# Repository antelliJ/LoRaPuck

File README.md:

# ESP32-C3 Lora Puck Device
https://github.com/antelliJ/LoRaPuck

A LoRa project built using an esp32-c3 supermini and an SX1262 for LoRa communication

## Features
- LoRa
    - Transmits +22 Dbm
    - 150-960 MHz
    - IPEX SMD connector
- Bluetooth Low Energy (BLE)
- WiFi (not implemented)
- 0.96" OLED display (optional)
    - I2C SSD1306

## Usage and info
there isn't a battery configuration setup, so everything is powered by wire. Check out the installation instructions below on further details on flashing builds.

### Purpose
LoRa and MeshCore are cool projects that use radio in an interesting way, and have a decently low barrier to entry with all the tools available. This project is the product of that.

## Hardware
- esp32-c3 supermini
- SX1262
- Generic SSD1306 0.96" OLED display modules with 2.54mm pin headers

## Firmware
### Schematic

### GPIO Assignment

| Signal   |   | ESP32-C3 GPIO |
|----------|---|---------------|
| SX NRST  |   | GPIO 5        |
| SX MISO  |   | GPIO 6        |
| SX MOSI  |   | GPIO 7        |
| SX NSS   |   | GPIO 10       |
| SX SCLK  |   | GPIO 1        |
| SX DIO1  |   | GPIO 0        |
| SX BUSY  |   | GPIO 4        |
|          |   |               |
| OLED SCL |   | GPIO 8        |
| OLED SDA |   | GPIO 3        |

### Installation Instructions

### For most people (recommended)
Get the latest stable firmware from the [Releases Page](https://github.com/antelliJ/LoRaPuck/releases)

The [Mescore flasher](https://meshcore.io/flasher) also has the ability to flash custom `.bin` files, so you can flash the bin files to your device there

This is paired with a MeshCore Client, for instance through the web, the mobile app, or for PC

Using the companion BLE build, you can flash firmware that you can connect to with your phone.
From here it should be able to be the same as any other campanion MeshCore device.

### For Devs
- Install [PlatformIO](https://docs.platformio.org/) in VS Code
- Clone the repository, and build and run one of the configurations through PlatformIO

- or to build a merged bin, run: (replace `AntelliPuck_companion_radio_ble` with the environment you want to build)
`pio pkg exec -p tool-esptoolpy -- esptool.py --chip esp32 merge_bin -o merged.bin --flash_mode dio --flash_size 4MB 0x0 .pio/build/AntelliPuck_companion_radio_ble/bootloader.bin 0x8000 .pio/build/AntelliPuck_companion_radio_ble/partitions.bin 0x10000 .pio/build/AntelliPuck_companion_radio_ble/firmware.bin`

### MeshCore Compatability
Theoretically it should work like any other MeshCore project, I'd personally go with the companion app for ease of communication.

## PCB
`\PCB\` includes files relevant for the schematic, PCB design, and manufacturing. 
`\PCB\production\` are the files used for PCB manufacturing

### PCB Renders

## CAD Model

Files for a model for the enclosure for this project can be found in `\3dModel\`.
`\3dModel\` is intended for all 3d printed related files.
`\3dModel\editable\` contains the editable files made in freecad for the enclosure
`\3dModel\printable\` contains the print ready files as a `.3mf` file

## Bill of Materials
A nicely formatted excel sheet is provided at `\PCB\production\ereader-bom.xlsx` with a few more comments. 
The below is just a static version of that...

| Designator  | Footprint                           | Quantity | Value             | LCSC Part # | Other Notes                                                                                                    |
|-------------|-------------------------------------|----------|-------------------|-------------|----------------------------------------------------------------------------------------------------------------|
| AE1         | U.FL_Hirose_U.FL-R-SMT-1_Vertical   | 1        | Antenna           | C88374      | Regular UFL / IPEX connector                                                                                   |
| C1, C2      | 402                                 | 2        | 100nF             |             |                                                                                                                |
| C10, C11    | 402                                 | 2        | 4.7pF             |             |                                                                                                                |
| C12, C13    | 402                                 | 2        | 1.5pF             |             |                                                                                                                |
| C14         | 402                                 | 1        | 2.7pF             |             |                                                                                                                |
| C15         | 402                                 | 1        | 100pF             |             |                                                                                                                |
| C16, C8, C9 | 402                                 | 3        | 3.3pF             |             |                                                                                                                |
| C3          | 603                                 | 1        | 470nF             |             |                                                                                                                |
| C4          | 603                                 | 1        | 47nF              |             |                                                                                                                |
| C5          | 402                                 | 1        | 47pF              |             |                                                                                                                |
| C6          | 402                                 | 1        | 1nF               |             |                                                                                                                |
| C7          | 402                                 | 1        | 33pF              |             |                                                                                                                |
| L1, L2      | 402                                 | 2        | 47nH              |             |                                                                                                                |
| L3          | 402                                 | 1        | 15nH              |             |                                                                                                                |
| L4          | 402                                 | 1        | 7.5nH             |             |                                                                                                                |
| L5          | 402                                 | 1        | 12nH              |             |                                                                                                                |
| R1          | 603                                 | 1        | 100               |             |                                                                                                                |
| U1          | QFN-24-1EP_4x4mm_P0.5mm_EP2.6x2.6mm | 1        | SX1262IMLTRT      |             |                                                                                                                |
| U2          | COMM-SMD_16P-L22.5-W18.0-P2.54-TL   | 1        | ESP32C3-SUPERMINI |             | [https://www.aliexpress.com/item/1005005757810089.html](https://www.aliexpress.com/item/1005005757810089.html) |
| U5          | PinHeader_1x04_P2.54mm_Vertical     | 1        | OLED_0.96_128x64  |             | [https://www.aliexpress.com/item/1005006141235306.html](https://www.aliexpress.com/item/1005006141235306.html) |
| U6          | SOT-363_SC-70-6                     | 1        | PE4259            |             |                                                                                                                |
| Y1          | Crystal_SMD_3225-4Pin_3.2x2.5mm     | 1        | 32 MHz            |             |                                                                                                                |

## References

Built using [this guide](https://blueprint.hackclub.com/starter-projects/lora)
While looking at supported MeshCore firmware I found [this one](https://github.com/ndoo/ikoka-stick-meshtastic-device) that looks really similar to what I wanted to achieve for this project, and I got a lot of inspiration for this readme from that project!
[This youtube video](https://www.youtube.com/watch?v=TnRn3Kn_aXg) for learning about RF PCB design

Firmware a copy from [MeshCore's repository](https://github.com/meshcore-dev/meshcore)

used [Table to Markdown](https://tabletomarkdown.com/convert-spreadsheet-to-markdown/) to make the above BOM in the readme

alongside [Markdown Table Formatter](http://markdowntable.com/) to make the markdown look better while editing source

### AI usage:
- Drafting PlatformIO commands for building a merged file

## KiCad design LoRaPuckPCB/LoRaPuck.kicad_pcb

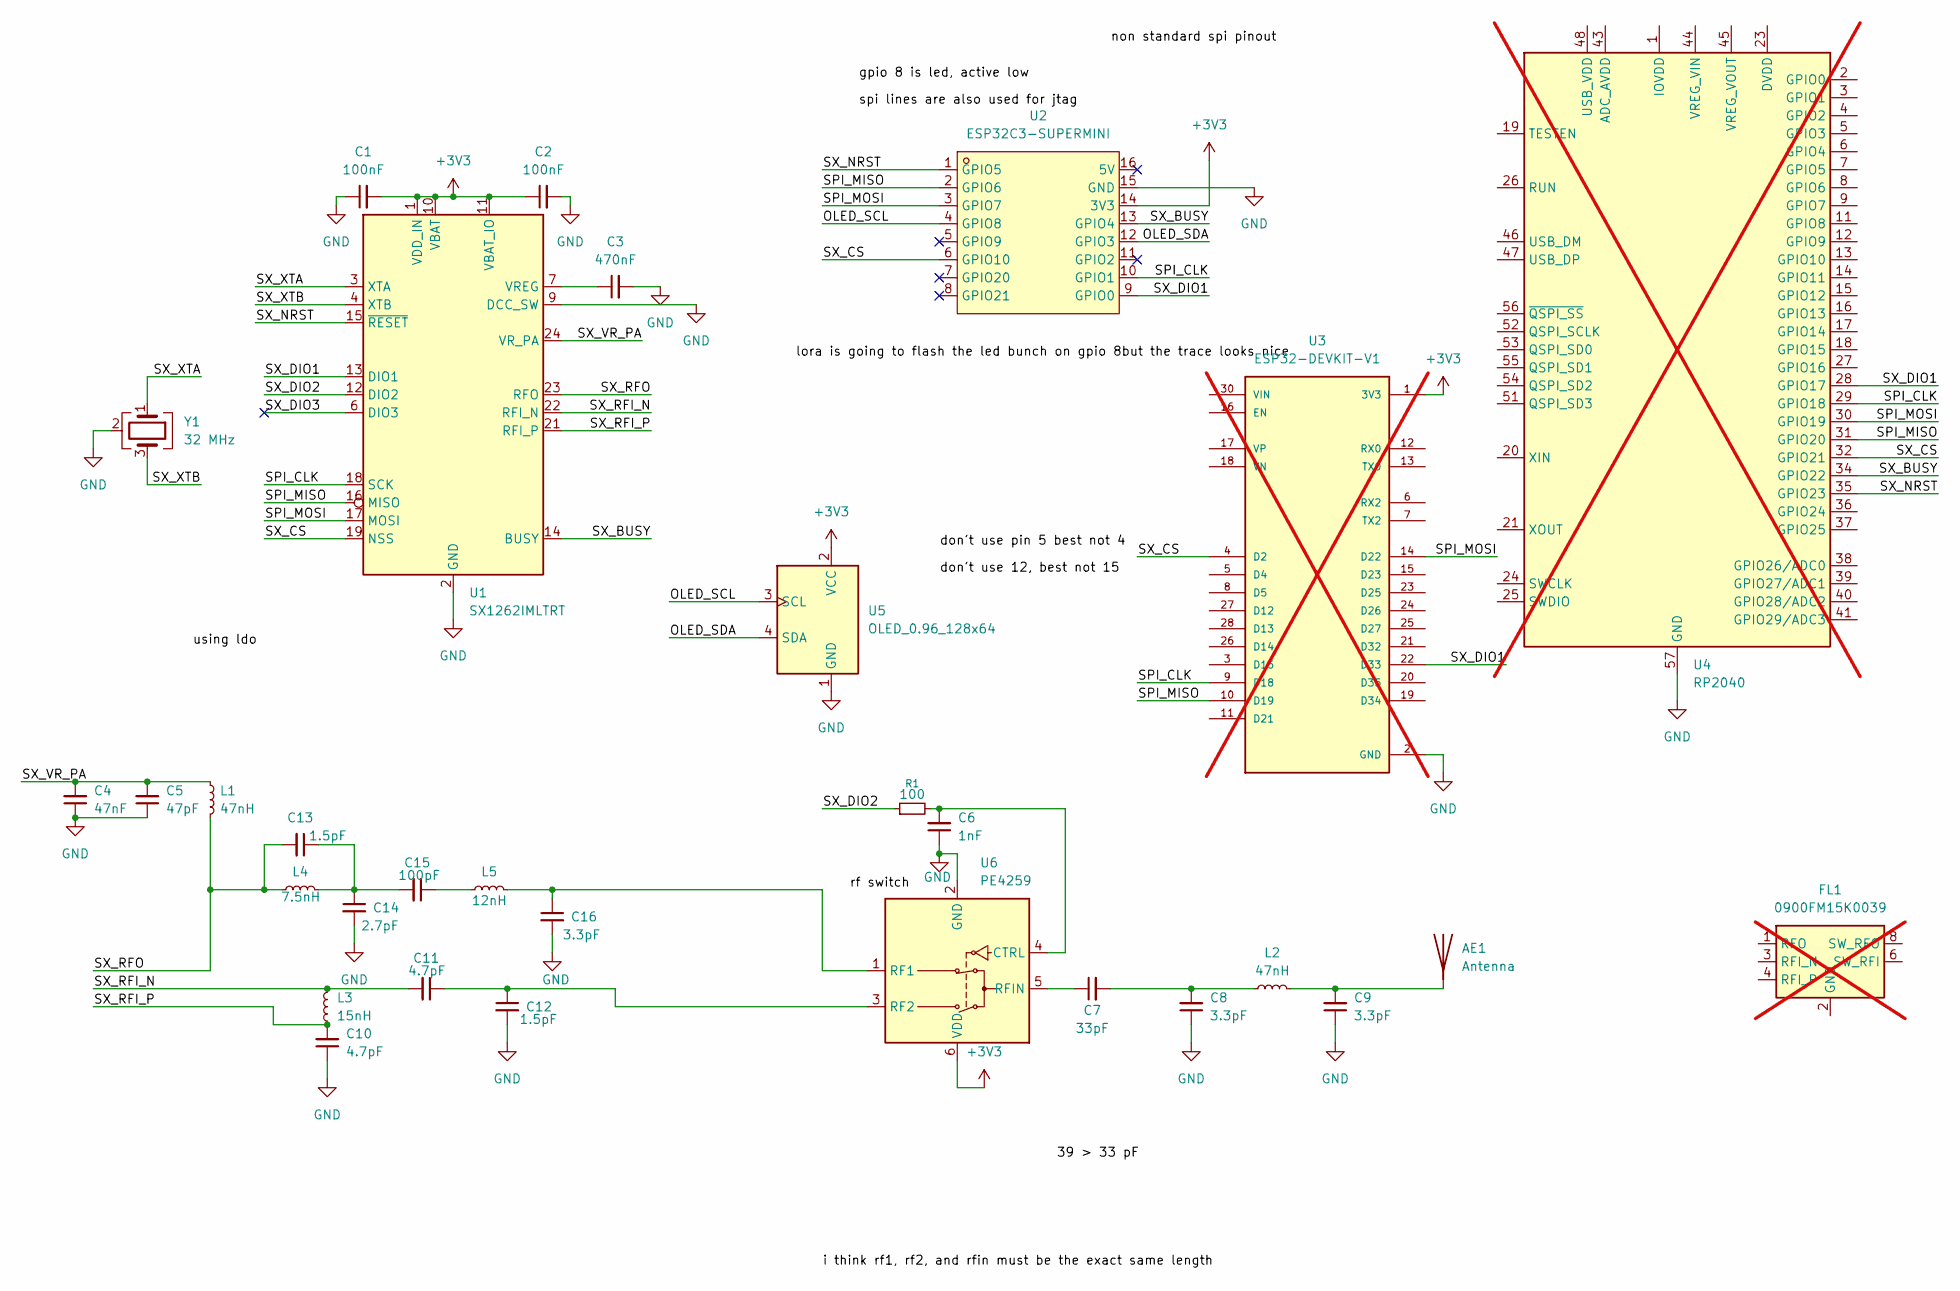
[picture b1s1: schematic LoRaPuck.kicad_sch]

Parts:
AE1: Antenna; U.FL_Hirose_U.FL-R-SMT-1_Vertical
C1, C2: 100nF; C_0402_1005Metric
C3: 470nF; C_0603_1608Metric
C4: 47nF; C_0603_1608Metric
C5: 47pF; C_0402_1005Metric
C6: 1nF; C_0402_1005Metric
C7: 33pF; C_0402_1005Metric
C8, C9, C16: 3.3pF; C_0402_1005Metric
C10, C11: 4.7pF; C_0402_1005Metric
C12, C13: 1.5pF; C_0402_1005Metric
C14: 2.7pF; C_0402_1005Metric
C15: 100pF; C_0402_1005Metric
FL1: 0900FM15K0039; Balun_Johanson_0900FM15K0039; not fitted
L1, L2: 47nH; L_0402_1005Metric
L3: 15nH; L_0402_1005Metric
L4: 7.5nH; L_0402_1005Metric
L5: 12nH; L_0402_1005Metric
R1: 100; R_0603_1608Metric
U1: SX1262IMLTRT; QFN-24-1EP_4x4mm_P0.5mm_EP2.6x2.6mm
U2: ESP32C3-SUPERMINI; COMM-SMD_16P-L22.5-W18.0-P2.54-TL; MPN ESP32C3-SuperMini; LCSC Part C9900147397
U3: ESP32-DEVKIT-V1; MODULE_ESP32_DEVKIT_V1; PARTREV N/A; not fitted
U4: RP2040; QFN-56-1EP_7x7mm_P0.4mm_EP3.2x3.2mm; not fitted
U5: OLED_0.96_128x64; PinHeader_1x04_P2.54mm_Vertical
U6: PE4259; SOT-363_SC-70-6
Y1: 32 MHz; Crystal_SMD_3225-4Pin_3.2x2.5mm

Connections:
+3V3: C1.2, C2.1, U1.1 (VDD_IN), U1.10 (VBAT), U1.11 (VBAT_IO), U2.14 (3V3), U3.1 (3V3), U5.2 (VCC), U6.6 (VDD)
/OLED_SCL: U2.4 (GPIO8), U5.3 (SCL)
/OLED_SDA: U2.12 (GPIO3), U5.4 (SDA)
/SPI_CLK: U1.18 (SCK), U2.10 (GPIO1), U3.9 (D18), U4.29 (GPIO18)
/SPI_MISO: U1.16 (MISO), U2.2 (GPIO6), U3.10 (D19), U4.31 (GPIO20)
/SPI_MOSI: U1.17 (MOSI), U2.3 (GPIO7), U3.14 (D22), U4.30 (GPIO19)
/SX_BUSY: U1.14 (BUSY), U2.13 (GPIO4), U4.34 (GPIO22)
/SX_CS: U1.19 (NSS), U2.6 (GPIO10), U3.4 (D2), U4.32 (GPIO21)
/SX_DIO1: U1.13 (DIO1), U2.9 (GPIO0), U3.22 (D33), U4.28 (GPIO17)
/SX_DIO2: R1.1, U1.12 (DIO2)
/SX_DIO3: U1.6 (DIO3)
/SX_NRST: U1.15 (~RESET), U2.1 (GPIO5), U4.35 (GPIO23)
/SX_RFI_N: C11.2, L3.2, U1.22 (RFI_N)
/SX_RFI_P: C10.2, L3.1, U1.21 (RFI_P)
/SX_RFO: C13.2, L1.2, L4.1, U1.23 (RFO)
/SX_VR_PA: C4.2, C5.2, L1.1, U1.24 (VR_PA)
/SX_XTA: U1.3 (XTA), Y1.1
/SX_XTB: U1.4 (XTB), Y1.3
GND: C1.1, C2.2, C3.2, C4.1, C5.1, C6.1, C8.1, C9.1, C10.1, C12.2, C14.2, C16.2, U1.2 (GND), U1.5 (GND), U1.8 (GND), U1.9 (DCC_SW), U1.20 (GND), U1.25 (GND), U2.15 (GND), U3.2 (GND), U3.29 (GND), U4.57 (GND), U5.1 (GND), U6.2 (GND), Y1.2 (G), Y1.4 (G)
unnamed: AE1.1 (A_1), C9.2, L2.2
unnamed: C7.2, C8.2, L2.1
unnamed: C13.1, C14.1, C15.2, L4.2
unnamed: C15.1, L5.1
unnamed: FL1.2 (GND), FL1.5 (GND), FL1.7 (GND), FL1.9 (GND), FL1.10 (GND)
unnamed: C3.1, U1.7 (VREG)
unnamed: U4.1 (IOVDD), U4.10 (IOVDD), U4.22 (IOVDD), U4.33 (IOVDD), U4.42 (IOVDD), U4.49 (IOVDD)
unnamed: U4.23 (DVDD), U4.50 (DVDD)
unnamed: C6.2, R1.2, U6.4 (CTRL)
unnamed: C16.1, L5.2, U6.1 (RF1)
unnamed: C11.1, C12.1, U6.3 (RF2)
unnamed: C7.1, U6.5 (RFIN)

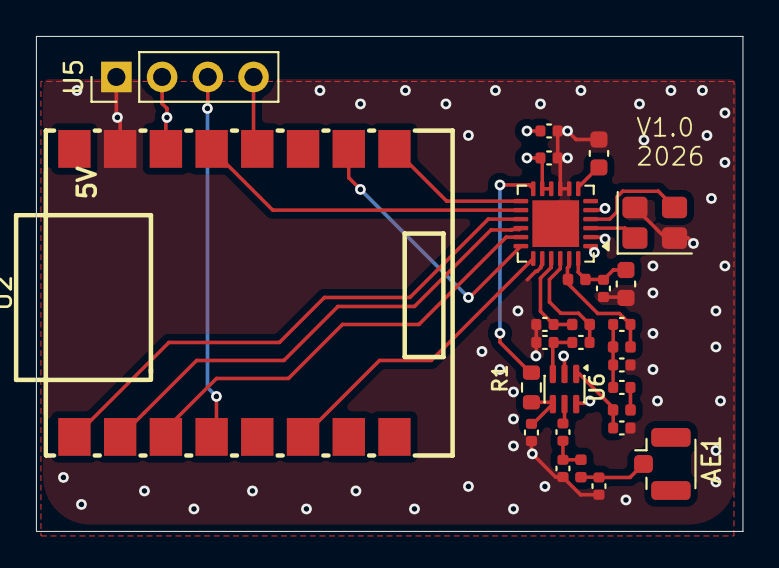
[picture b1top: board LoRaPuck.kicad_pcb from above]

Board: 4 copper layers, 39.2 x 27.5 mm, 28 parts (0 on the bottom side), 27 nets.

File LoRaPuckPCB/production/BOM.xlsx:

Designator | Footprint | Quantity | Value | LCSC Part # | Other Notes
AE1 | U.FL_Hirose_U.FL-R-SMT-1_Vertical | 1 | Antenna | C88374 | Regular UFL / IPEX connector
C1, C2 | 402 | 2 | 100nF
C10, C11 | 402 | 2 | 4.7pF
C12, C13 | 402 | 2 | 1.5pF
C14 | 402 | 1 | 2.7pF
C15 | 402 | 1 | 100pF
C16, C8, C9 | 402 | 3 | 3.3pF
C3 | 603 | 1 | 470nF
C4 | 603 | 1 | 47nF
C5 | 402 | 1 | 47pF
C6 | 402 | 1 | 1nF
C7 | 402 | 1 | 33pF
L1, L2 | 402 | 2 | 47nH
L3 | 402 | 1 | 15nH
L4 | 402 | 1 | 7.5nH
L5 | 402 | 1 | 12nH
R1 | 603 | 1 | 100
U1 | QFN-24-1EP_4x4mm_P0.5mm_EP2.6x2.6mm | 1 | SX1262IMLTRT
U2 | COMM-SMD_16P-L22.5-W18.0-P2.54-TL | 1 | ESP32C3-SUPERMINI |  | https://www.aliexpress.com/item/1005005757810089.html
U5 | PinHeader_1x04_P2.54mm_Vertical | 1 | OLED_0.96_128x64 |  | https://www.aliexpress.com/item/1005006141235306.html
U6 | SOT-363_SC-70-6 | 1 | PE4259
Y1 | Crystal_SMD_3225-4Pin_3.2x2.5mm | 1 | 32 MHz
